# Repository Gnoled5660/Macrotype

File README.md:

# Macrotype

# Description
This is a fully custom wireless hot swappable macropad with a custom Microcontroller. It has a total of nine fully custom programmable keyswitches and a rotary encoder as well as a 0.91 OLED display. It still remains pretty compact, while having that many components. It's size is approximately 10x6.8x1.6cm. There is a LiPo 3.7V Battery built in, but if you want to charge it, you can simply charge the battery via the USB-C receptacle. The macropad has an IC charger built in. If it is connected to the USB-C port, then the nRF52840 MCU chip, will be directly powered by the external power source, while the battery is being charged. However, if it is not connected to an external power supply, then the chip will be powered by the battery.

# Motivation
I have always wanted to design my own macropad, as it can be quite useful. I wanted to challenge myself a little bit, which is why I didn't choose a regular microcontroller and designed the entire board myself. 

# Assembling the macropad
It is quite straight forward to assemble everything. As the PCB will be preassembled by JLCPCB, since there are many components that cannot be hand soldered, there is not much to do on the soldering part. It is only necessary to solder the display and the rotary encoder onto the PCB and connect the Battery with the socket. There are four mounting holes on the PCB, that are used to screw screws onto the CAD model. For this project, you only need four M2 screws. It is also recommended to use heated threat inserts, to guarentee more grip.

# Schematic and Components
The main component is the nRF52840, a relatively cheap chip, that is capable of bluetooth low energy. This chip functions as the main processing unit, to handle all the actions that can be done with the board. Another important component is the BQ24074, it is an IC charger that can charge the battery, while still letting power to the MCU. As the battery is a 3.7V LiPo, the voltage always varies between 3.3V and 4.0V. Thats why there is also a Low Dropout Regulator, that convert the voltage to 3.3V.

Using this reference provided by nordic semiconductors, I was able to draw the schematic around the chip.

# PCB
The PCB is a 4 layer PCB, with the first and fourth layer function as signal transmitting layers. The second layer is a big Ground plane and the third layer is a hybrid layer with signal tracks and Ground planes. The most crucial part of the PCB is the radio frequency part. This part cannot have any tracks or Ground planes above or under it, as any distrubances might change the frequency.

# Firmware 
To flash the nRF52840 chip, you have to use a bootloader and connect it physically to the pin sockets on the board. There is a row with SWD sockets. Connect it to these rows and flash the Firmware onto it. You can find it in the folder Firmware. Afterwards, you can simply connect the chip via the USB-C port to a computer and upload the uf2 file, which contains all the keyboard settings and drag the files onto the chip. The keyboard firmware was built with ZMK.

# Firmware setup
The firmware was built with ZMK. After following the guide of ZMK of how to setup your own ZMK configuration GitHub repo, you have to change the board informations according to your needs. My custom Macropad includes having a rotary encoder, display and a 3x3 Matrix switches. You can find the configurations in detail in the ZMK config file.

# Case
The case consists of two different parts. The bottom part has four holes, where heated threat inserts can be inserted. There is a rectangle that stands out a little bit, so that it can be pressed in to the other part.

# BOM
|Reference           |Qty                          |Links                                                                                                                                                                                                                                                                                                                                                                                                                                                                                                                                                          |Value|Footprint|Description      |Price    |
|--------------------|-----------------------------|---------------------------------------------------------------------------------------------------------------------------------------------------------------------------------------------------------------------------------------------------------------------------------------------------------------------------------------------------------------------------------------------------------------------------------------------------------------------------------------------------------------------------------------------------------------|-----|---------|-----------------|---------|
|Crystal             |1                            |https://jlcpcb.com                                                                                                                                                                                                                                                                                                                                                                                                                                                                                                                                             |32.768kHz|Crystal:Crystal_SMD_3215-2Pin_3.2x1.5mm|Two pin crystal  |See below|
|Crystal             |1                            |https://jlcpcb.com                                                                                                                                                                                                                                                                                                                                                                                                                                                                                                                                             |32MHz|Crystal:Crystal_SMD_2016-4Pin_2.0x1.6mm|Two pin crystal  |See below|
|Low Dropout Regulator|1                            |https://jlcpcb.com                                                                                                                                                                                                                                                                                                                                                                                                                                                                                                                                             |MCP1700T-3302E_TT|MCP1700T-3302E_TT:SOT95P237X112-3N|Pwr Sply Func,Voltage Regulator,LDO,SOT-23,PD 369.6mW,VO 3.3V,Regline +/-0.75%/V &#124; Microchip Technology Inc. MCP1700T-3302E/TT|See below|
|IC Charger          |1                            |https://jlcpcb.com                                                                                                                                                                                                                                                                                                                                                                                                                                                                                                                                             |BQ24074RGTR|BQ24074RGTR:QFN50P300X300X100-17N|Standalone 1-cell 1.5-A linear battery charger, Power Path, 4.2-V VBAT, 10.5-V OVP and 4.4-V VOUT|See below|
|nRF52840            |1                            |https://jlcpcb.com                                                                                                                                                                                                                                                                                                                                                                                                                                                                                                                                             |NRF52840-QIAA-R|footprints:AQFN-73-1EP_7x7mm_P0.5mm_NRF52840-custom|IC RF TxRx + MCU 802.15.4, Bluetooth Bluetooth v5.0, Thread, Zigbee® 2.4GHz 73-VFQFN Dual Rows, Exposed Pad|See below|
|Rotary Encoder      |1                            |https://jlcpcb.com                                                                                                                                                                                                                                                                                                                                                                                                                                                                                                                                             |RotaryEncoder_Switch|Rotary_Encoder:RotaryEncoder_Alps_EC11E-Switch_Vertical_H20mm|Rotary encoder, dual channel, incremental quadrate outputs, with switch|See below|
|Button              |1                            |https://jlcpcb.com                                                                                                                                                                                                                                                                                                                                                                                                                                                                                                                                             |SW_Push|Button_Switch_SMD:SW_Push_1P1T_NO_CK_KMR2|Push button switch, generic, two pins|See below|
|Keyswitch           |9                            |https://jlcpcb.com                                                                                                                                                                                                                                                                                                                                                                                                                                                                                                                                             |Keyswitch|Switch_Keyboard_Hotswap_Kailh:SW_Hotswap_Kailh_MX|Push button switch, normally open, two pins, 45° tilted|See below|
|Resistor            |2                            |https://jlcpcb.com                                                                                                                                                                                                                                                                                                                                                                                                                                                                                                                                             |5.1k |Resistor_SMD:R_0402_1005Metric|Resistor         |See below|
|Resistor            |3                            |https://jlcpcb.com                                                                                                                                                                                                                                                                                                                                                                                                                                                                                                                                             |10k  |Resistor_SMD:R_0402_1005Metric|Resistor         |See below|
|Resistor            |1                            |https://jlcpcb.com                                                                                                                                                                                                                                                                                                                                                                                                                                                                                                                                             |47k  |Resistor_SMD:R_0402_1005Metric|Resistor         |See below|
|Resistor            |1                            |https://jlcpcb.com                                                                                                                                                                                                                                                                                                                                                                                                                                                                                                                                             |0    |Resistor_SMD:R_0402_1005Metric|Resistor         |See below|
|Resistor            |1                            |https://jlcpcb.com                                                                                                                                                                                                                                                                                                                                                                                                                                                                                                                                             |5.9k |Resistor_SMD:R_0402_1005Metric|Resistor         |See below|
|Resistor            |1                            |https://jlcpcb.com                                                                                                                                                                                                                                                                                                                                                                                                                                                                                                                                             |3.0k |Resistor_SMD:R_0402_1005Metric|Resistor         |See below|
|Resistor            |2                            |https://jlcpcb.com                                                                                                                                                                                                                                                                                                                                                                                                                                                                                                                                             |1.5k |Resistor_SMD:R_0402_1005Metric|Resistor         |See below|
|Inductor            |1                            |https://jlcpcb.com                                                                                                                                                                                                                                                                                                                                                                                                                                                                                                                                             |4.7nH|Inductor_SMD:L_0402_1005Metric|Inductor         |See below|
|USB-C Receptacle    |1                            |https://jlcpcb.com                                                                                                                                                                                                                                                                                                                                                                                                                                                                                                                                             |TYPE-C-31-M-12|TYPE-C-31-M-12:HRO_TYPE-C-31-M-12|USB Connectors 24 Receptacle 1 8.94*7.3mm RoHS|See below|
|JST Socket          |1                            |https://jlcpcb.com                                                                                                                                                                                                                                                                                                                                                                                                                                                                                                                                             |Conn_01x02_Socket|Connector_JST:JST_PH_S2B-PH-K_1x02_P2.00mm_Horizontal|Generic connector, single row, 01x02, script generated|See below|
|LED                 |2                            |https://jlcpcb.com                                                                                                                                                                                                                                                                                                                                                                                                                                                                                                                                             |LED  |LED_SMD:LED_0603_1608Metric|Light emitting diode|See below|
|Unpolarized Capcitor|1                            |https://jlcpcb.com                                                                                                                                                                                                                                                                                                                                                                                                                                                                                                                                             |820pF|Capacitor_SMD:C_0402_1005Metric|Unpolarized capacitor|See below|
|Unpolarized Capcitor|1                            |https://jlcpcb.com                                                                                                                                                                                                                                                                                                                                                                                                                                                                                                                                             |1.5pF|Capacitor_SMD:C_0402_1005Metric|Unpolarized capacitor|See below|
|Unpolarized Capcitor|1                            |https://jlcpcb.com                                                                                                                                                                                                                                                                                                                                                                                                                                                                                                                                             |0.5pF|Capacitor_SMD:C_0402_1005Metric|Unpolarized capacitor|See below|
|Unpolarized Capcitor|1                            |https://jlcpcb.com                                                                                                                                                                                                                                                                                                                                                                                                                                                                                                                                             |0.8pF|Capacitor_SMD:C_0402_1005Metric|Unpolarized capacitor|See below|
|Unpolarized Capcitor|1                            |https://jlcpcb.com                                                                                                                                                                                                                                                                                                                                                                                                                                                                                                                                             |100pF|Capacitor_SMD:C_0402_1005Metric|Unpolarized capacitor|See below|
|Unpolarized Capcitor|2                            |https://jlcpcb.com                                                                                                                                                                                                                                                                                                                                                                                                                                                                                                                                             |N.C. |Capacitor_SMD:C_0402_1005Metric|Unpolarized capacitor|See below|
|Unpolarized Capcitor|1                            |https://jlcpcb.com                                                                                                                                                                                                                                                                                                                                                                                                                                                                                                                                             |1.0uF|Capacitor_SMD:C_0603_1608Metric|Unpolarized capacitor|See below|
|Unpolarized Capcitor|4                            |https://jlcpcb.com                                                                                                                                                                                                                                                                                                                                                                                                                                                                                                                                             |1uF  |Capacitor_SMD:C_0603_1608Metric|Unpolarized capacitor|See below|
|Unpolarized Capcitor|3                            |https://jlcpcb.com                                                                                                                                                                                                                                                                                                                                                                                                                                                                                                                                             |100nF|Capacitor_SMD:C_0402_1005Metric|Unpolarized capacitor|See below|
|Unpolarized Capcitor|4                            |https://jlcpcb.com                                                                                                                                                                                                                                                                                                                                                                                                                                                                                                                                             |12pF |Capacitor_SMD:C_0402_1005Metric|Unpolarized capacitor|See below|
|Unpolarized Capcitor|4                            |https://jlcpcb.com                                                                                                                                                                                                                                                                                                                                                                                                                                                                                                                                             |4.7uF|Capacitor_SMD:C_0603_1608Metric|Unpolarized capacitor|See below|
|0.91 Display        |1                            |https://www.roboter-bausatz.de/p/0.91-oled-display-blau-128-32-ssd1306-i2c-modul-fuer-arduino-raspberry-pi?number=RBS17395&weiche=2&bid=284037-112606-CjwKCAjwxb7RBhA5EiwAQ-AAdFHQgZO50lI-4mJakAwufHefXGeRBqagyHlzbb7zqNV4eCwBOuO-URoCDh8QAvD_BwE%4083&adcref=t.adcell.com%2F                                                                                                                                                                                                                                                                                  |     |         |Oled Display 128x32|4        |
|Hot Swappable Sockets|50                           |https://amazon.com                                                                                                                                                                                                                                                                                                                                                                                                                                                                                                                                             |     |         |Kailh CPG151101S11 Hot Swappable PCB Socket|10       |
|PCB with all Components|1                            |https://jlcpcb.com                                                                                                                                                                                                                                                                                                                                                                                                                                                                                                                                             |     |         |5x PCB fully assembled|110      |
|Filament            |                             |                                                                                                                                                                                                                                                                                                                                                                                                                                                                                                                                                               |     |         | 40g             | 0.5     |
|total               |                             |                                                                                                                                                                                                                                                                                                                                                                                                                                                                                                                                                               |     |         |                 |124      |

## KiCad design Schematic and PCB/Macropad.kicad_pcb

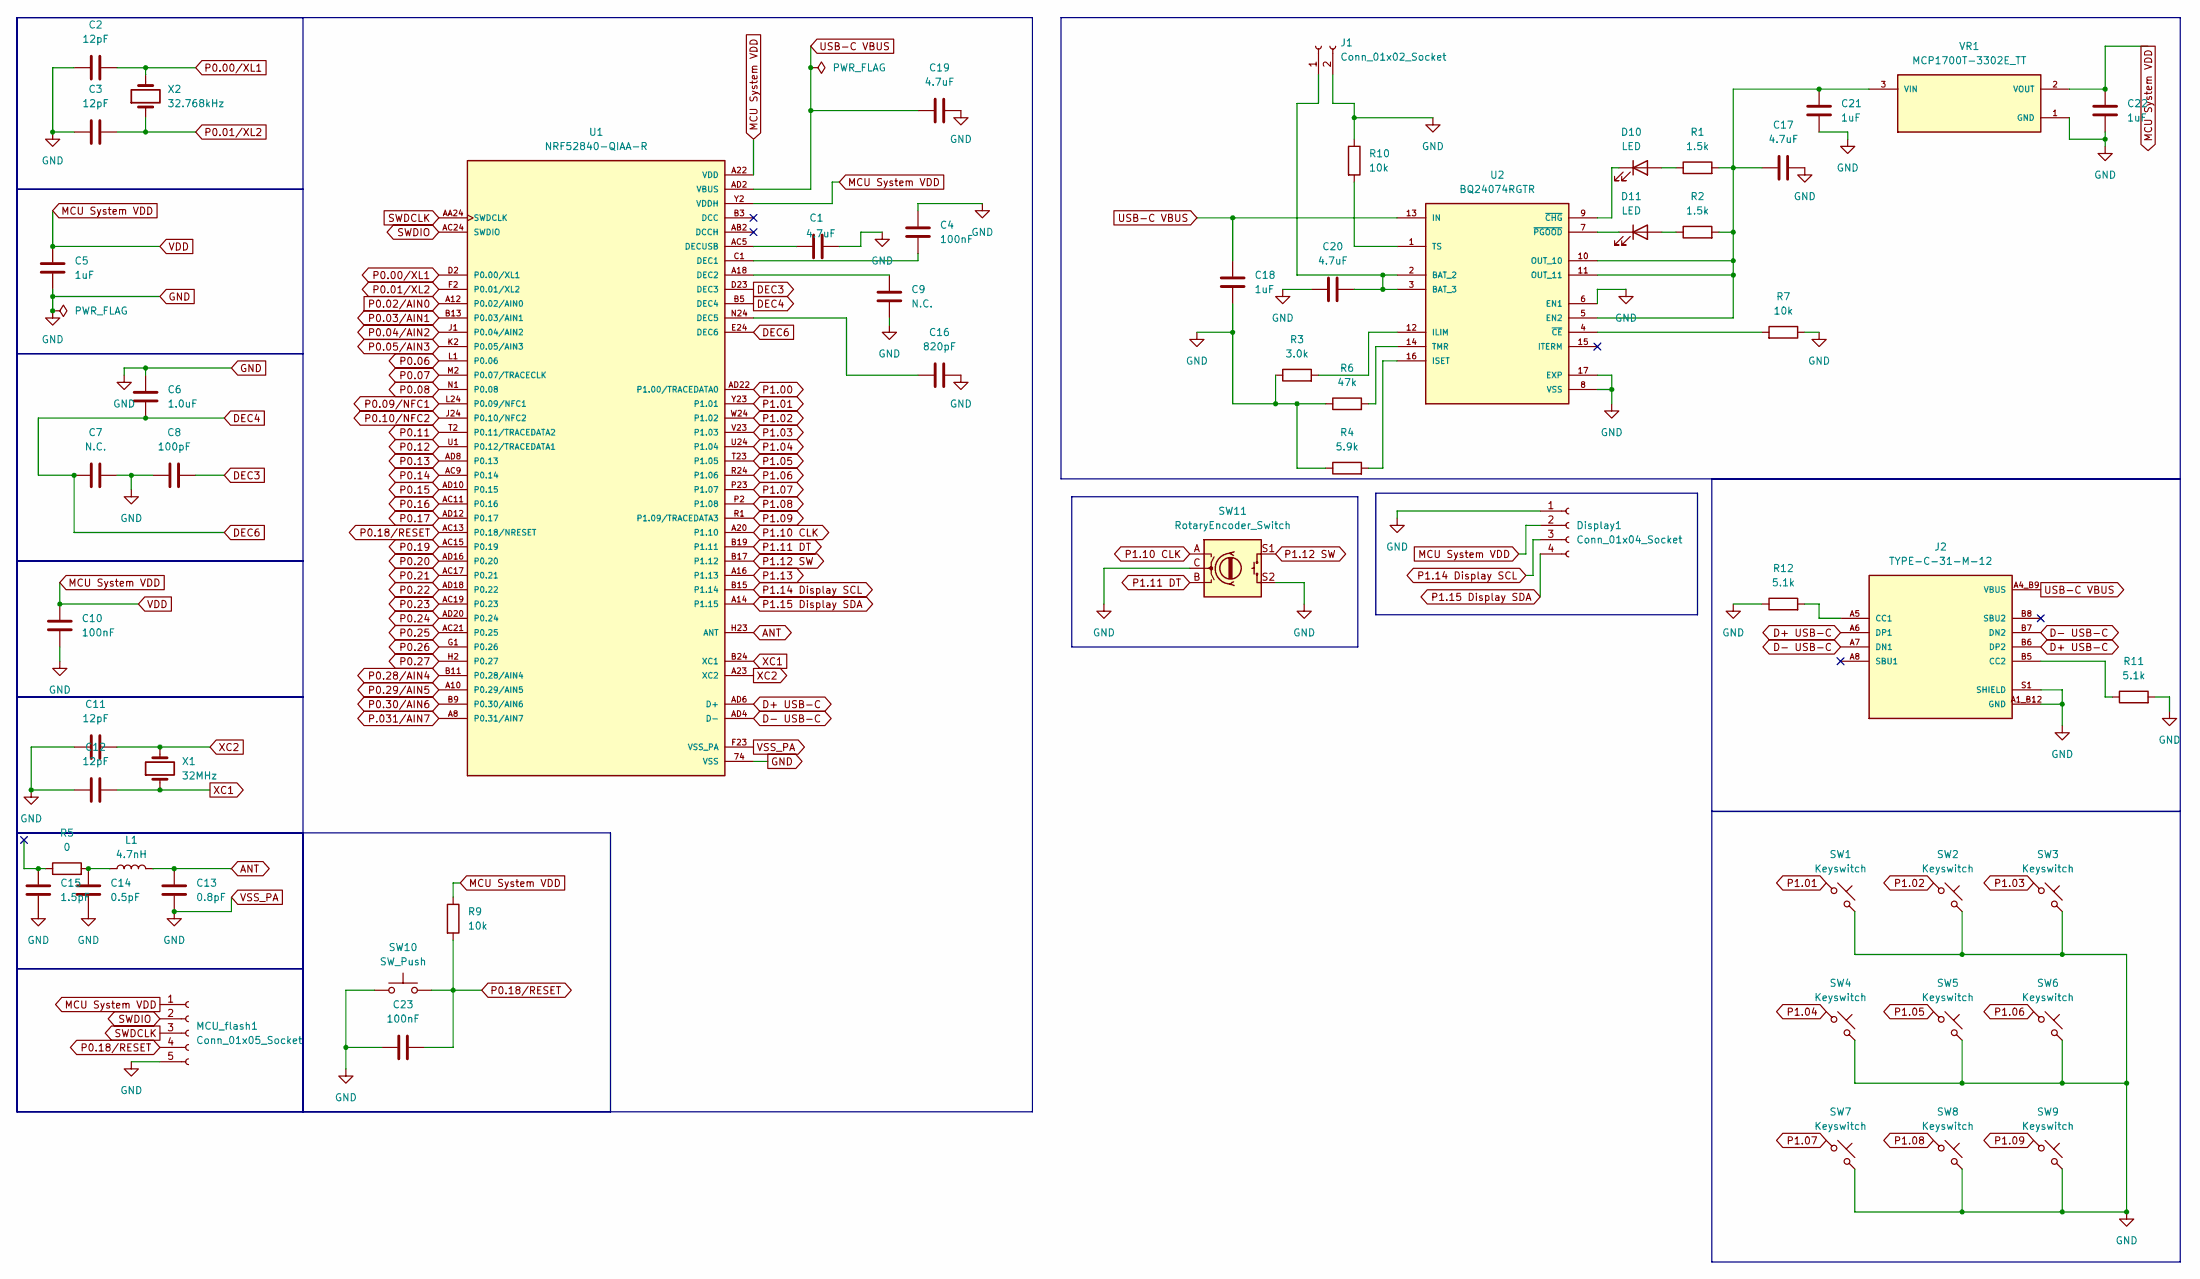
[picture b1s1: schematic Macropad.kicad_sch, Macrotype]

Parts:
C1, C17, C19, C20: 4.7uF; C_0603_1608Metric
C2, C3, C11, C12: 12pF; C_0402_1005Metric
C4, C10, C23: 100nF; C_0402_1005Metric
C5, C18, C21, C22: 1uF; C_0603_1608Metric
C6: 1.0uF; C_0603_1608Metric
C7, C9: N.C.; C_0402_1005Metric
C8: 100pF; C_0402_1005Metric
C13: 0.8pF; C_0402_1005Metric
C14: 0.5pF; C_0402_1005Metric
C15: 1.5pF; C_0402_1005Metric
C16: 820pF; C_0402_1005Metric
D10, D11: LED; LED_0603_1608Metric
Display1: Conn_01x04_Socket; PinHeader_1x04_P2.54mm_Vertical
J1: Conn_01x02_Socket; JST_PH_S2B-PH-K_1x02_P2.00mm_Horizontal
J2: TYPE-C-31-M-12; HRO_TYPE-C-31-M-12; PARTREV 2020.12.08
L1: 4.7nH; L_0402_1005Metric
MCU_flash1: Conn_01x05_Socket; PinHeader_1x05_P2.54mm_Vertical
R1, R2: 1.5k; R_0402_1005Metric
R3: 3.0k; R_0402_1005Metric
R4: 5.9k; R_0402_1005Metric
R5: 0; R_0402_1005Metric
R6: 47k; R_0402_1005Metric
R7, R9, R10: 10k; R_0402_1005Metric
R11, R12: 5.1k; R_0402_1005Metric
SW1, SW2, SW3, SW4, SW5, SW6, SW7, SW8, SW9: Keyswitch; SW_Hotswap_Kailh_MX
SW10: SW_Push; SW_Push_1P1T_NO_CK_KMR2
SW11: RotaryEncoder_Switch; RotaryEncoder_Alps_EC11E-Switch_Vertical_H20mm
U1: NRF52840-QIAA-R; AQFN-73-1EP_7x7mm_P0.5mm_NRF52840-custom; PARTREV v1.1
U2: BQ24074RGTR; QFN50P300X300X100-17N; PARTREV M
VR1: MCP1700T-3302E_TT; SOT95P237X112-3N; PARTREV E
X1: 32MHz; Crystal_SMD_2016-4Pin_2.0x1.6mm
X2: 32.768kHz; Crystal_SMD_3215-2Pin_3.2x1.5mm

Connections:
/ANT: C15.1, R5.1
ANT: C13.1, L1.2, U1.H23 (ANT)
D+ USB-C: J2.A6 (DP1), J2.B6 (DP2), U1.AD6 (D+)
D- USB-C: J2.A7 (DN1), J2.B7 (DN2), U1.AD4 (D-)
DEC3: C8.2, U1.D23 (DEC3)
DEC4: C6.2, C7.1, U1.B5 (DEC4), U1.E24 (DEC6)
GND: C1.2, C2.1, C3.1, C4.1, C5.2, C6.1, C7.2, C8.1, C9.2, C10.2, C11.1, C12.1, C13.2, C14.2, C15.2, C16.1, C17.2, C18.2, C19.2, C20.1, C21.1, C22.2, C23.1, Display1.1, J1.2, J2.A1_B12 (GND), J2.B1_A12 (GND), J2.S1 (SHIELD), J2.S2 (SHIELD), J2.S3 (SHIELD), J2.S4 (SHIELD), MCU_flash1.5, R3.1, R4.1, R6.1, R7.1, R10.1, R11.2, R12.1, SW1.2, SW2.2, SW3.2, SW4.2, SW5.2, SW6.2, SW7.2, SW8.2, SW9.2, SW10.1, SW11.C, SW11.S2, U1.74 (VSS), U1.B7 (VSS), U1.F23 (VSS_PA), U2.6 (EN1), U2.8 (VSS), U2.17 (EXP), U2.18, U2.19, U2.20, U2.21, U2.22, VR1.1 (GND)
MCU System VDD: C5.1, C10.1, C22.1, Display1.2, MCU_flash1.1, R9.1, U1.A22 (VDD), U1.AD14 (VDD), U1.AD23 (VDD), U1.B1 (VDD), U1.W1 (VDD), U1.Y2 (VDDH), VR1.2 (VOUT)
unnamed: C14.1, L1.1, R5.2
unnamed: D10.2 (A), R1.1
unnamed: D10.1 (K), U2.9 (~CHG)
unnamed: D11.2 (A), R2.1
unnamed: D11.1 (K), U2.7 (~PGOOD)
unnamed: C20.2, J1.1, U2.2 (BAT_2), U2.3 (BAT_3)
unnamed: J2.A5 (CC1), R12.2
unnamed: J2.B5 (CC2), R11.1
unnamed: C4.2, U1.C1 (DEC1)
unnamed: C9.1, U1.A18 (DEC2)
unnamed: C16.2, U1.N24 (DEC5)
unnamed: C1.1, U1.AC5 (DECUSB)
unnamed: C17.1, C21.2, R1.2, R2.2, U2.5 (EN2), U2.10 (OUT_10), U2.11 (OUT_11), VR1.3 (VIN)
unnamed: R3.2, U2.12 (ILIM)
unnamed: R4.2, U2.16 (ISET)
unnamed: R6.2, U2.14 (TMR)
unnamed: R10.2, U2.1 (TS)
unnamed: R7.2, U2.4 (~CE)
P0.00/XL1: C2.2, U1.D2 (P0.00/XL1), X2.2
P0.01/XL2: C3.2, U1.F2 (P0.01/XL2), X2.1
P0.02/AIN0: U1.A12 (P0.02/AIN0)
P0.03/AIN1: U1.B13 (P0.03/AIN1)
P0.04/AIN2: U1.J1 (P0.04/AIN2)
P0.05/AIN3: U1.K2 (P0.05/AIN3)
P0.06: U1.L1 (P0.06)
P0.07: U1.M2 (P0.07/TRACECLK)
P0.08: U1.N1 (P0.08)
P0.09/NFC1: U1.L24 (P0.09/NFC1)
P0.10/NFC2: U1.J24 (P0.10/NFC2)
P0.11: U1.T2 (P0.11/TRACEDATA2)
P0.12: U1.U1 (P0.12/TRACEDATA1)
P0.13: U1.AD8 (P0.13)
P0.14: U1.AC9 (P0.14)
P0.15: U1.AD10 (P0.15)
P0.16: U1.AC11 (P0.16)
P0.17: U1.AD12 (P0.17)
P0.18/RESET: C23.2, MCU_flash1.4, R9.2, SW10.2, U1.AC13 (P0.18/NRESET)
P0.19: U1.AC15 (P0.19)
P0.20: U1.AD16 (P0.20)
P0.21: U1.AC17 (P0.21)
P0.22: U1.AD18 (P0.22)
P0.23: U1.AC19 (P0.23)
P0.24: U1.AD20 (P0.24)
P0.25: U1.AC21 (P0.25)
P0.26: U1.G1 (P0.26)
P0.27: U1.H2 (P0.27)
P0.28/AIN4: U1.B11 (P0.28/AIN4)
P0.29/AIN5: U1.A10 (P0.29/AIN5)
P0.30/AIN6: U1.B9 (P0.30/AIN6)
P1.00: U1.AD22 (P1.00/TRACEDATA0)
P1.01: SW1.1, U1.Y23 (P1.01)
P1.02: SW2.1, U1.W24 (P1.02)
P1.03: SW3.1, U1.V23 (P1.03)
P1.04: SW4.1, U1.U24 (P1.04)
P1.05: SW5.1, U1.T23 (P1.05)
P1.06: SW6.1, U1.R24 (P1.06)
P1.07: SW7.1, U1.P23 (P1.07)
P1.08: SW8.1, U1.P2 (P1.08)
P1.09: SW9.1, U1.R1 (P1.09/TRACEDATA3)
P1.10 CLK: SW11.A, U1.A20 (P1.10)
P1.11 DT: SW11.B, U1.B19 (P1.11)
P1.12 SW: SW11.S1, U1.B17 (P1.12)
P1.13: U1.A16 (P1.13)
P1.14 Display SCL: Display1.3, U1.B15 (P1.14)
P1.15 Display SDA: Display1.4, U1.A14 (P1.15)
P.031/AIN7: U1.A8 (P0.31/AIN7)
SWDCLK: MCU_flash1.3, U1.AA24 (SWDCLK)
SWDIO: MCU_flash1.2, U1.AC24 (SWDIO)
USB-C VBUS: C18.1, C19.1, J2.A4_B9 (VBUS), J2.B4_A9 (VBUS), U1.AD2 (VBUS), U2.13 (IN)
XC1: C12.2, U1.B24 (XC1), X1.1
XC2: C11.2, U1.A23 (XC2), X1.2

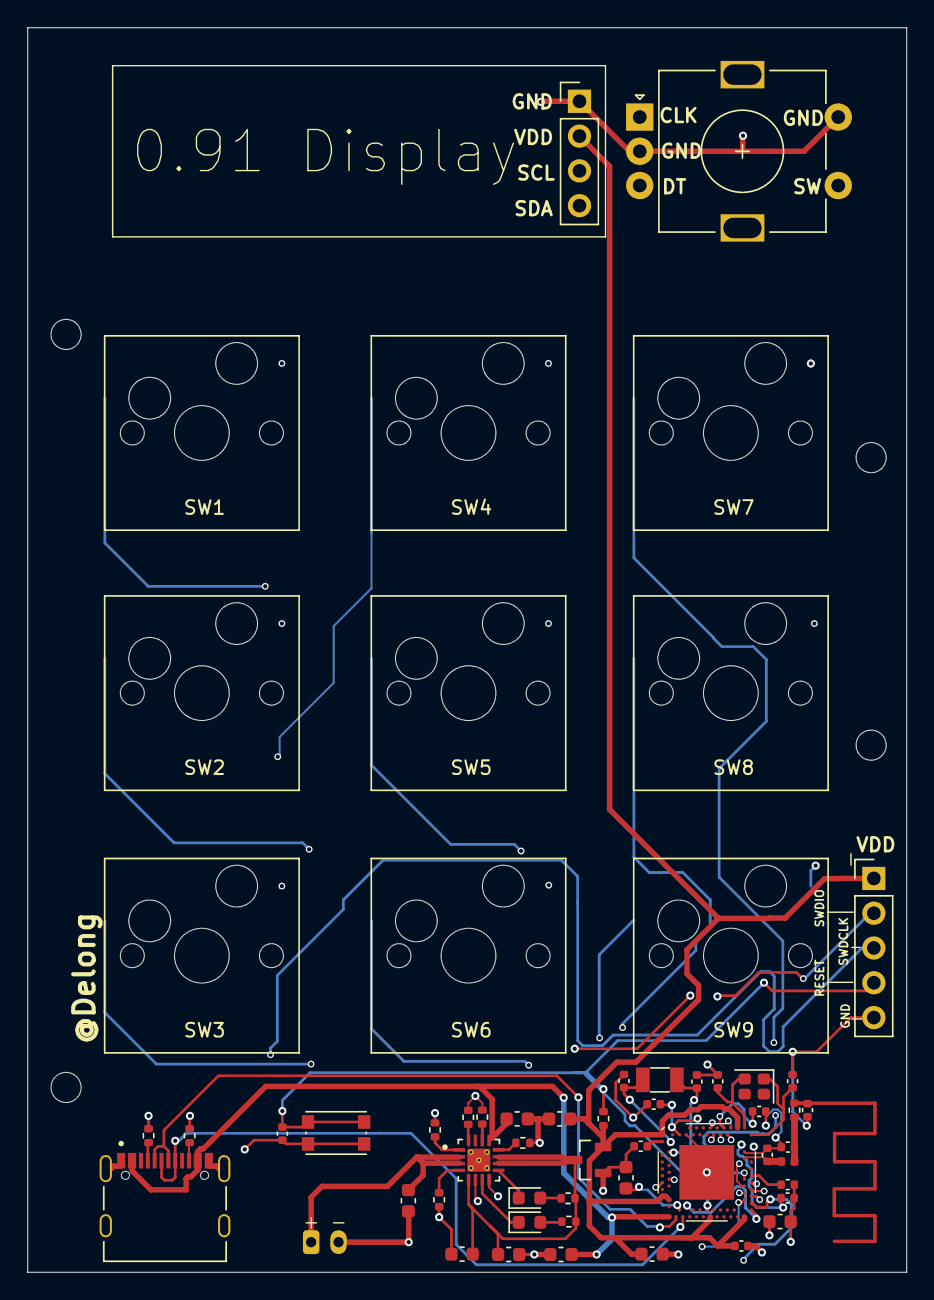
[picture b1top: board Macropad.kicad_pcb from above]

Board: 4 copper layers, 64.2 x 90.9 mm, 57 parts (1 on the bottom side), 48 nets.

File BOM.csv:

Reference,Qty,Links,Value,Footprint,Description,Price
Crystal,1,https://jlcpcb.com,32.768kHz,Crystal:Crystal_SMD_3215-2Pin_3.2x1.5mm,Two pin crystal,See below
Crystal,1,https://jlcpcb.com,32MHz,Crystal:Crystal_SMD_2016-4Pin_2.0x1.6mm,Two pin crystal,See below
Low Dropout Regulator,1,https://jlcpcb.com,MCP1700T-3302E_TT,MCP1700T-3302E_TT:SOT95P237X112-3N,"Pwr Sply Func,Voltage Regulator,LDO,SOT-23,PD 369.6mW,VO 3.3V,Regline +/-0.75%/V | Microchip Technology Inc. MCP1700T-3302E/TT",See below
IC Charger,1,https://jlcpcb.com,BQ24074RGTR,BQ24074RGTR:QFN50P300X300X100-17N,"Standalone 1-cell 1.5-A linear battery charger, Power Path, 4.2-V VBAT, 10.5-V OVP and 4.4-V VOUT",See below
nRF52840,1,https://jlcpcb.com,NRF52840-QIAA-R,footprints:AQFN-73-1EP_7x7mm_P0.5mm_NRF52840-custom,"IC RF TxRx + MCU 802.15.4, Bluetooth Bluetooth v5.0, Thread, Zigbee® 2.4GHz 73-VFQFN Dual Rows, Exposed Pad",See below
Rotary Encoder,1,https://jlcpcb.com,RotaryEncoder_Switch,Rotary_Encoder:RotaryEncoder_Alps_EC11E-Switch_Vertical_H20mm,"Rotary encoder, dual channel, incremental quadrate outputs, with switch",See below
Button,1,https://jlcpcb.com,SW_Push,Button_Switch_SMD:SW_Push_1P1T_NO_CK_KMR2,"Push button switch, generic, two pins",See below
Keyswitch,9,https://jlcpcb.com,Keyswitch,Switch_Keyboard_Hotswap_Kailh:SW_Hotswap_Kailh_MX,"Push button switch, normally open, two pins, 45° tilted",See below
Resistor,2,https://jlcpcb.com,5.1k,Resistor_SMD:R_0402_1005Metric,Resistor,See below
Resistor,3,https://jlcpcb.com,10k,Resistor_SMD:R_0402_1005Metric,Resistor,See below
Resistor,1,https://jlcpcb.com,47k,Resistor_SMD:R_0402_1005Metric,Resistor,See below
Resistor,1,https://jlcpcb.com,0,Resistor_SMD:R_0402_1005Metric,Resistor,See below
Resistor,1,https://jlcpcb.com,5.9k,Resistor_SMD:R_0402_1005Metric,Resistor,See below
Resistor,1,https://jlcpcb.com,3.0k,Resistor_SMD:R_0402_1005Metric,Resistor,See below
Resistor,2,https://jlcpcb.com,1.5k,Resistor_SMD:R_0402_1005Metric,Resistor,See below
Inductor,1,https://jlcpcb.com,4.7nH,Inductor_SMD:L_0402_1005Metric,Inductor,See below
USB-C Receptacle,1,https://jlcpcb.com,TYPE-C-31-M-12,TYPE-C-31-M-12:HRO_TYPE-C-31-M-12,USB Connectors 24 Receptacle 1 8.94*7.3mm RoHS,See below
JST Socket,1,https://jlcpcb.com,Conn_01x02_Socket,Connector_JST:JST_PH_S2B-PH-K_1x02_P2.00mm_Horizontal,"Generic connector, single row, 01x02, script generated",See below
LED,2,https://jlcpcb.com,LED,LED_SMD:LED_0603_1608Metric,Light emitting diode,See below
Unpolarized Capcitor,1,https://jlcpcb.com,820pF,Capacitor_SMD:C_0402_1005Metric,Unpolarized capacitor,See below
Unpolarized Capcitor,1,https://jlcpcb.com,1.5pF,Capacitor_SMD:C_0402_1005Metric,Unpolarized capacitor,See below
Unpolarized Capcitor,1,https://jlcpcb.com,0.5pF,Capacitor_SMD:C_0402_1005Metric,Unpolarized capacitor,See below
Unpolarized Capcitor,1,https://jlcpcb.com,0.8pF,Capacitor_SMD:C_0402_1005Metric,Unpolarized capacitor,See below
Unpolarized Capcitor,1,https://jlcpcb.com,100pF,Capacitor_SMD:C_0402_1005Metric,Unpolarized capacitor,See below
Unpolarized Capcitor,2,https://jlcpcb.com,N.C.,Capacitor_SMD:C_0402_1005Metric,Unpolarized capacitor,See below
Unpolarized Capcitor,1,https://jlcpcb.com,1.0uF,Capacitor_SMD:C_0603_1608Metric,Unpolarized capacitor,See below
Unpolarized Capcitor,4,https://jlcpcb.com,1uF,Capacitor_SMD:C_0603_1608Metric,Unpolarized capacitor,See below
Unpolarized Capcitor,3,https://jlcpcb.com,100nF,Capacitor_SMD:C_0402_1005Metric,Unpolarized capacitor,See below
Unpolarized Capcitor,4,https://jlcpcb.com,12pF,Capacitor_SMD:C_0402_1005Metric,Unpolarized capacitor,See below
Unpolarized Capcitor,4,https://jlcpcb.com,4.7uF,Capacitor_SMD:C_0603_1608Metric,Unpolarized capacitor,See below
0.91 Display,1,https://www.roboter-bausatz.de/p/0.91-oled-display-blau-128-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,,,Oled Display 128x32,4
Hot Swappable Sockets,50,https://amazon.com,,,Kailh CPG151101S11 Hot Swappable PCB Socket,10
PCB with all Components,1,https://jlcpcb.com,,,5x PCB fully assembled,110
total,,,,,,124

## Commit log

2026-06-13 Create code
2026-06-13 Rename macropad-nice_nano_v2-zmk.uf2 to macropad-zmk.uf2
2026-06-13 Create w
2026-06-13 Update ZMK config
2026-06-15 Rename Copy of fallout_zine_template.pdf-7.pdf to Zine.pdf
2026-06-15 Rename Copy of fallout_zine_template-7.png to Zine.png
2026-06-17 Add BOM section to README.md
    Added a Bill of Materials (BOM) section with component details and links.
